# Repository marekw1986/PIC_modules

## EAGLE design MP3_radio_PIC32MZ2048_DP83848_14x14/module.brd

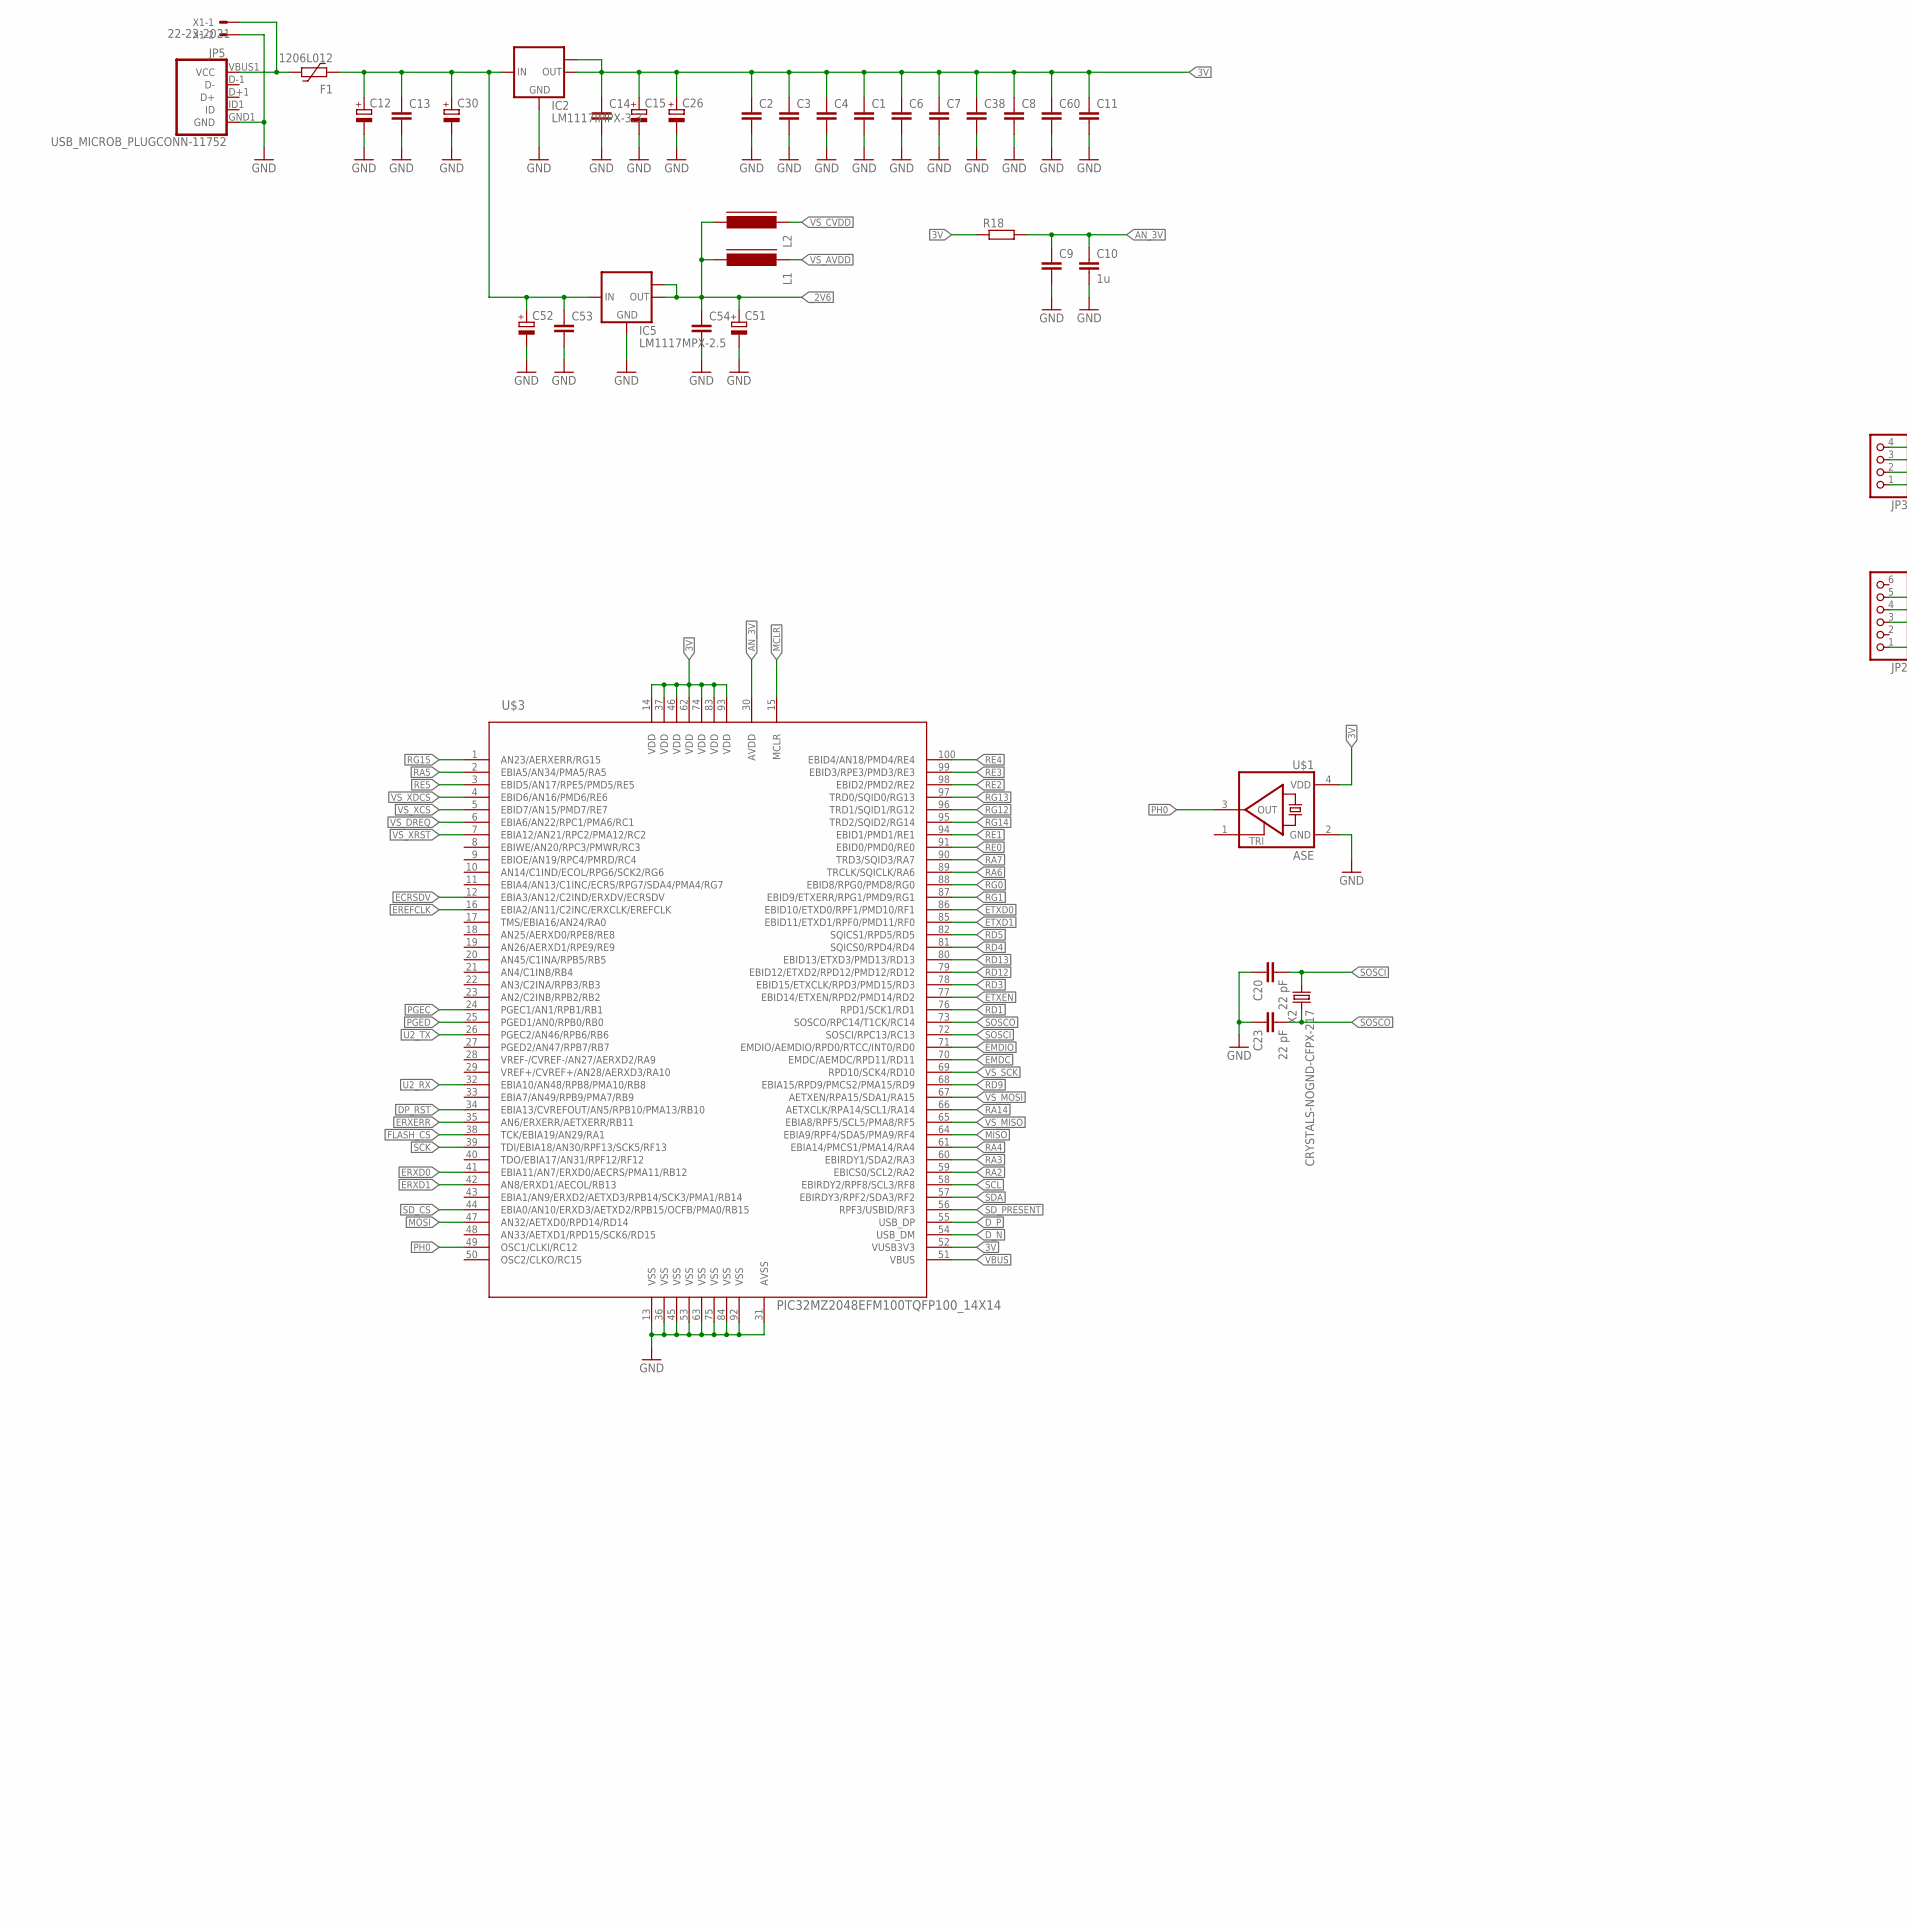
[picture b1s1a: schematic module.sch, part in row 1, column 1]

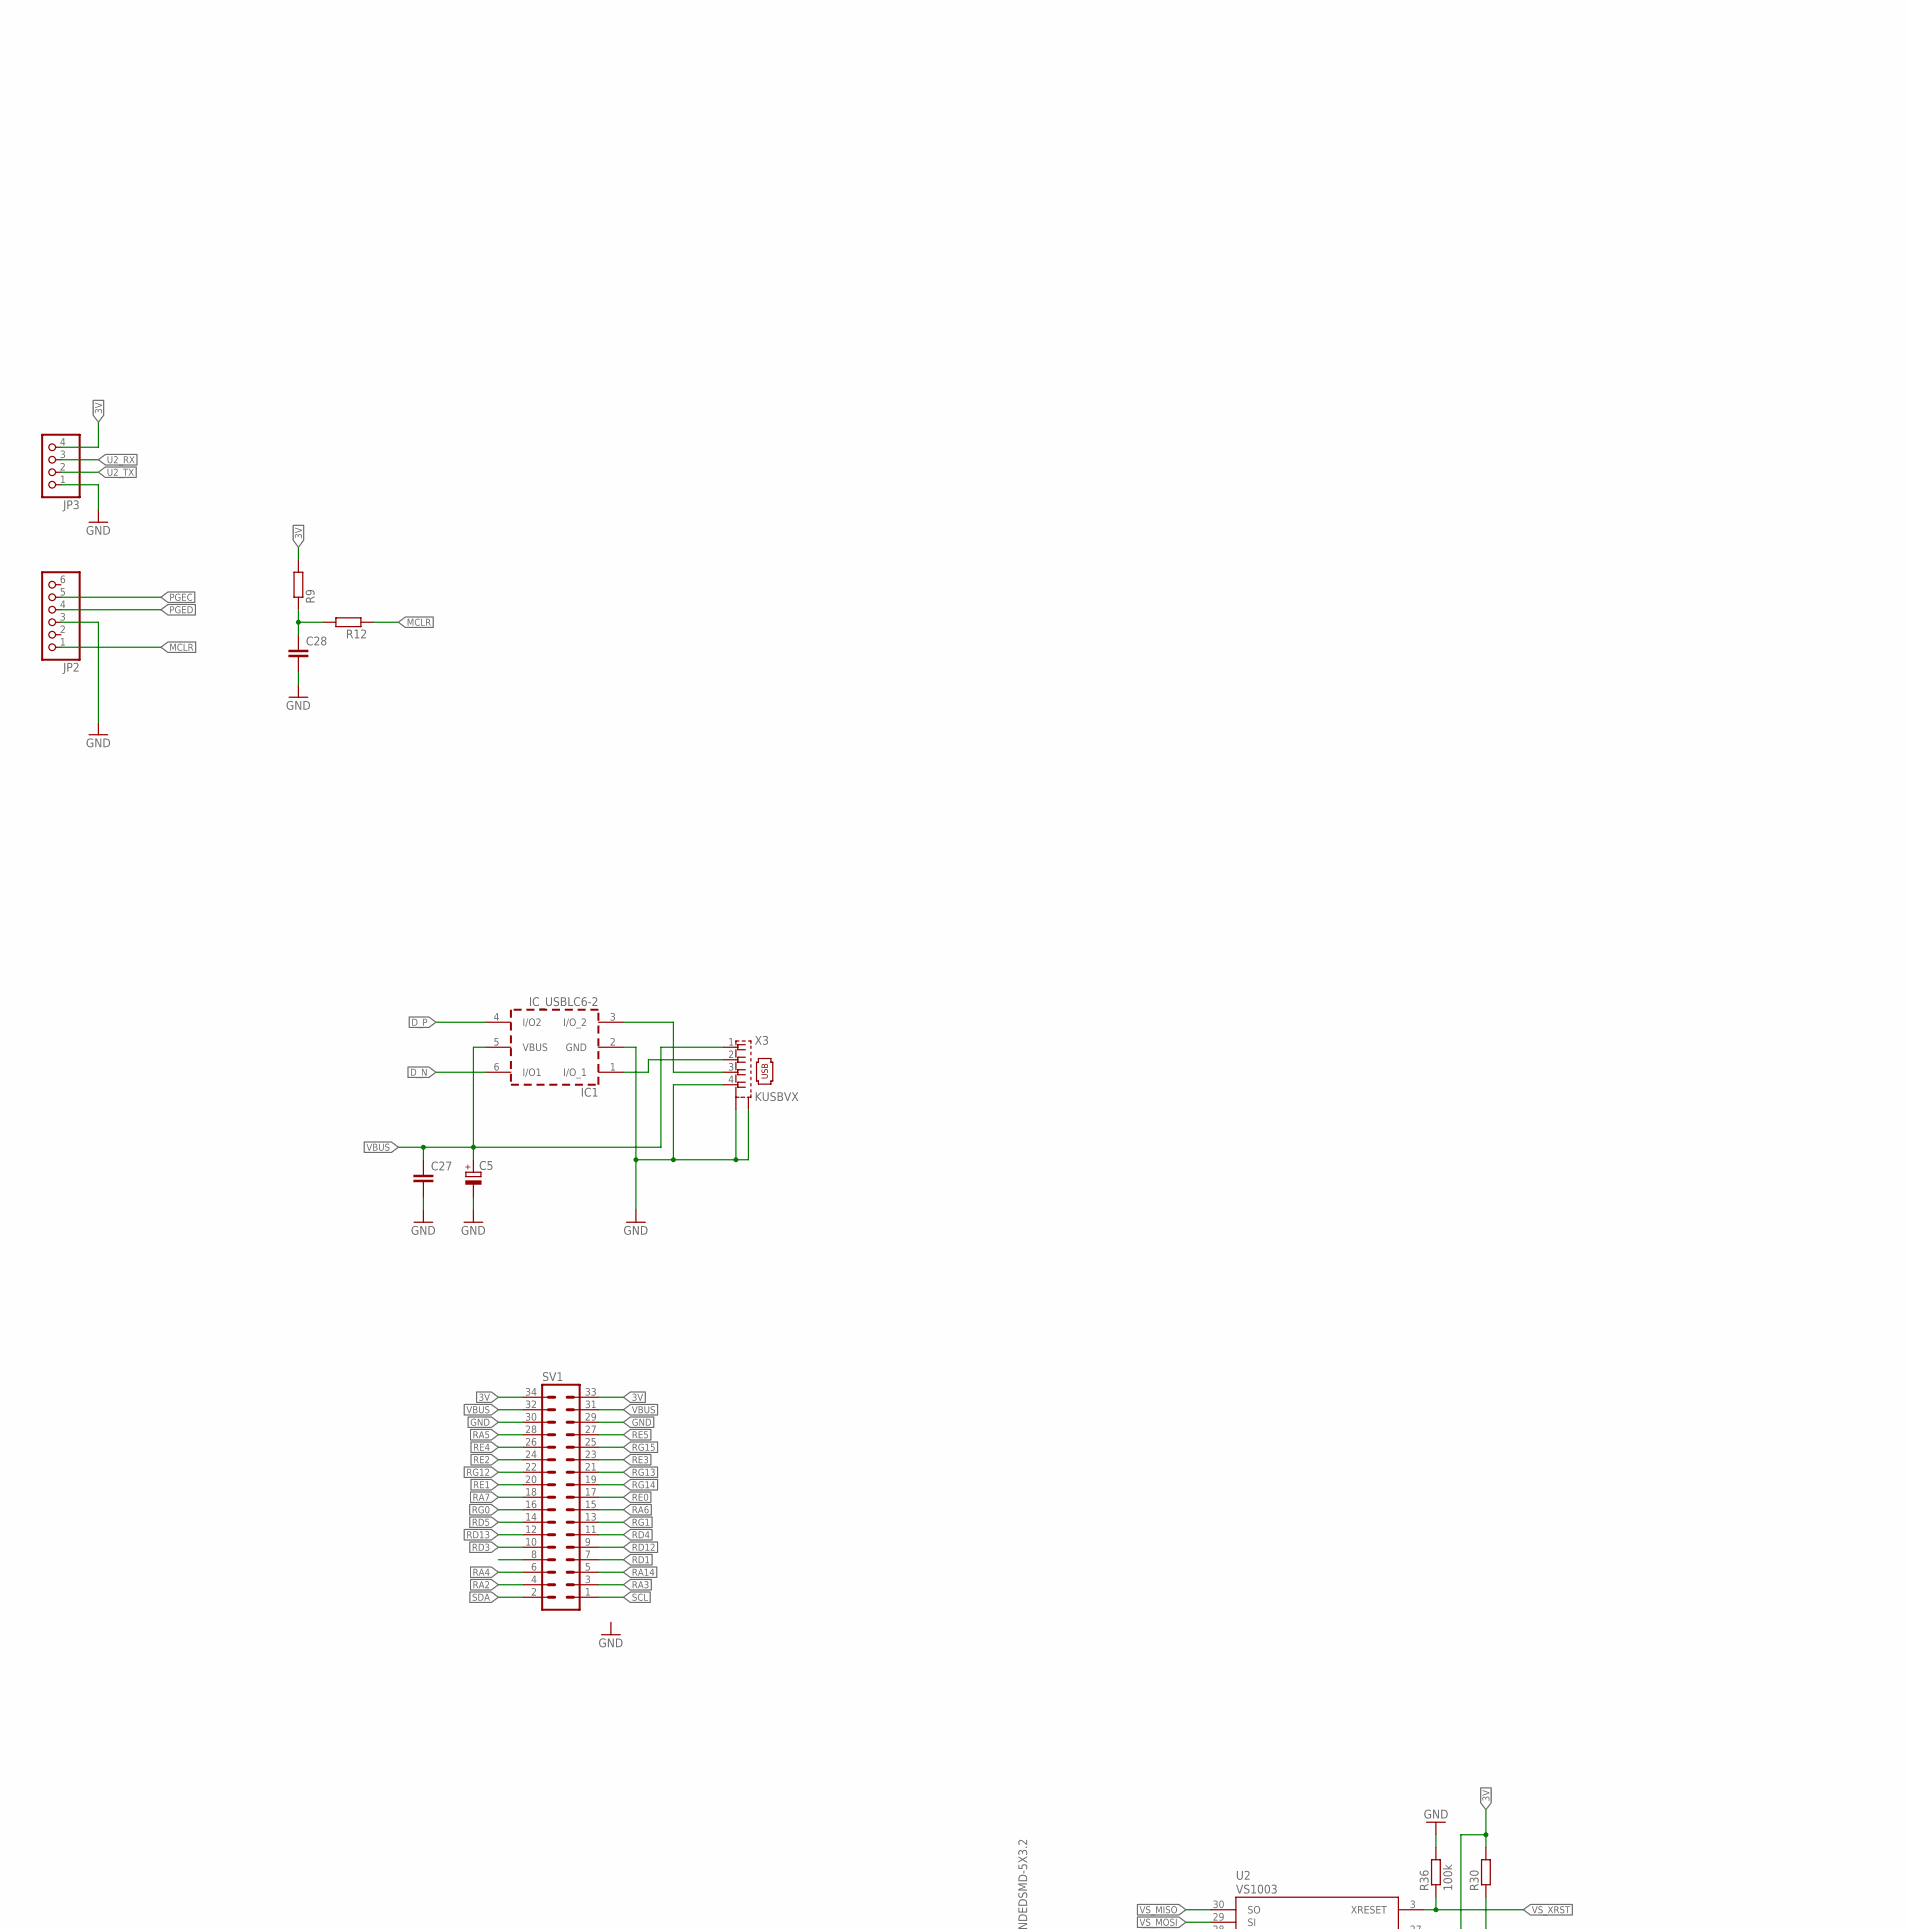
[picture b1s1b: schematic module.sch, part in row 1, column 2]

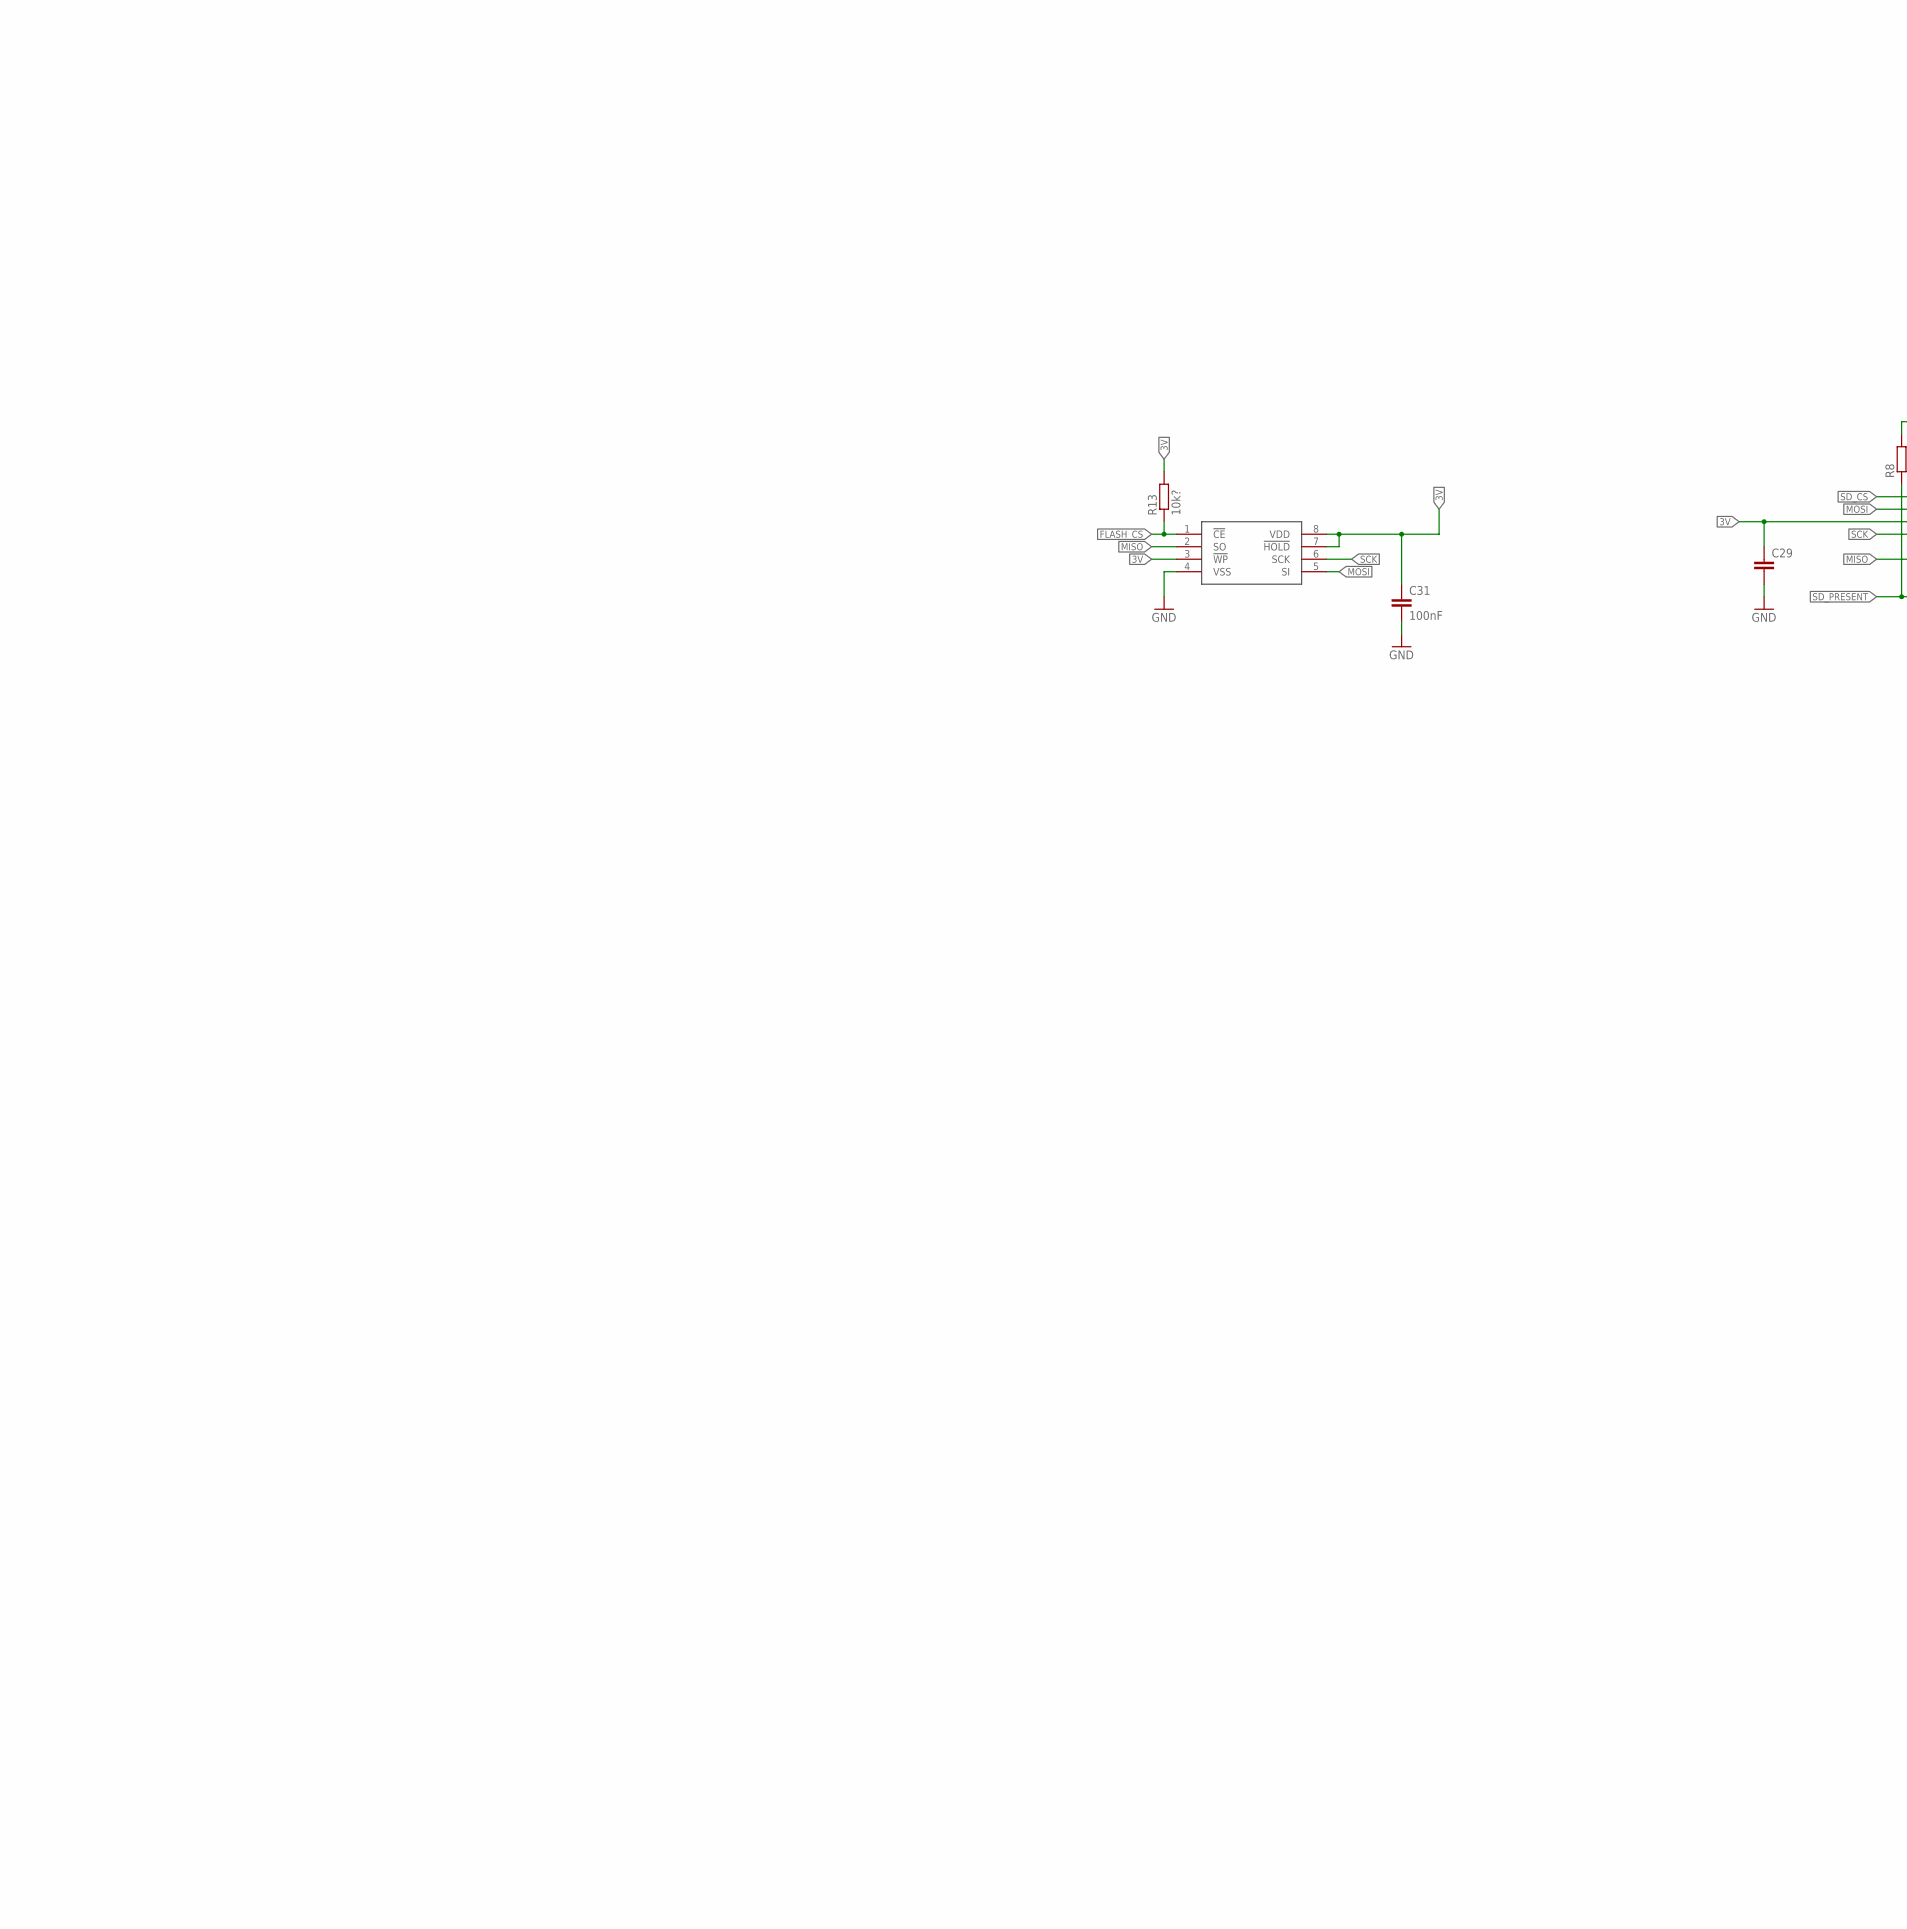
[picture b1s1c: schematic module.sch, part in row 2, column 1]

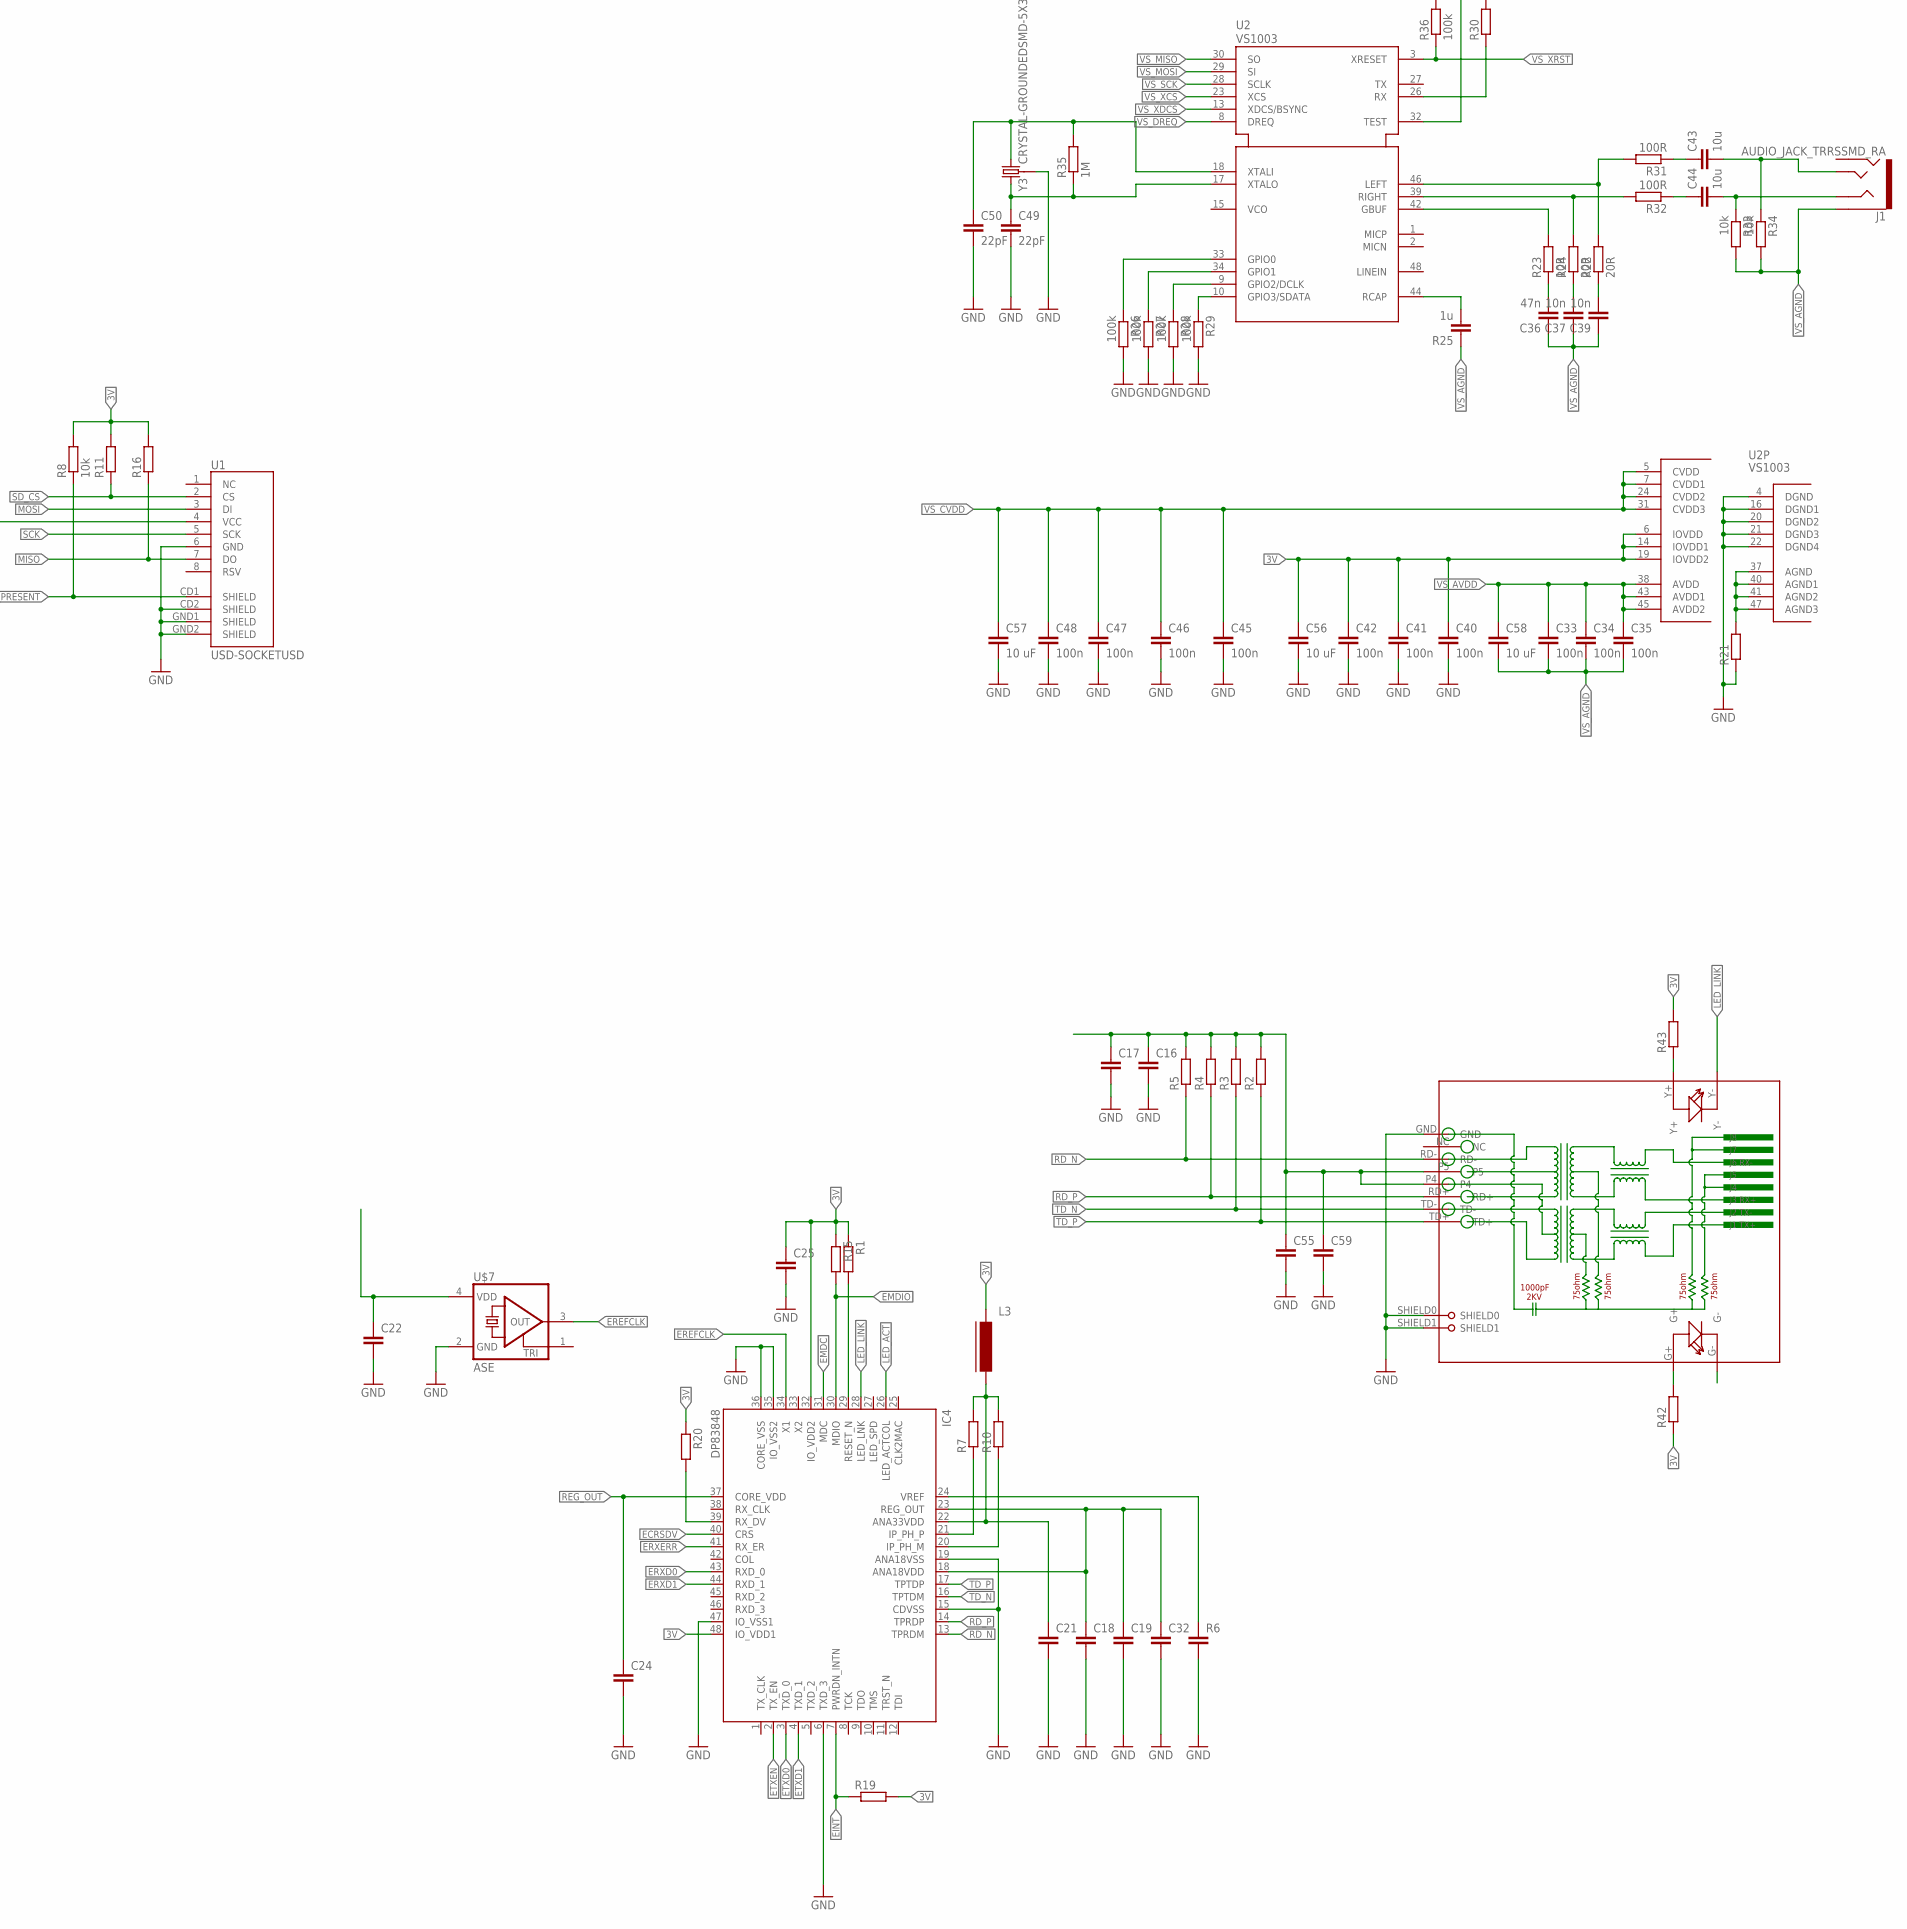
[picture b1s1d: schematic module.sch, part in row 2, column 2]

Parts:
C1, C2, C3, C4, C6, C7, C8, C9, C11, C18, C19, C21, C22, C38, C60: C-EUC0402; C0402
C5, C26, C30: CPOL-EUSMCA; SMC_A
C10: 1u; C0603
C12, C15, C51, C52: CPOL-EUSMCB; SMC_B
C13, C14, C16, C17, C24, C25, C27, C28, C29, C32, C55, C59: C-EUC0603; C0603
C20, C23: 22 pF; C0603
C31: 100nF; C0603
C33, C34, C35, C46, C47, C48: 100n; C0603
C36: 47n; C0603
C37, C39: 10n; C0603
C40, C41, C42, C45: 100n; C0402
C43, C44: 10u; C0603
C49, C50: 22pF; C0603
C53, C54: C-EUC1206; C1206
C56, C57, C58: 10 uF; C0603
F1: 1206L012; 1206L
IC1: IC_USBLC6-2; SOT-23-6L
IC2: LM1117IMPX-3.3; SOT223
IC4: DP83848; LQFP48
IC5: LM1117MPX-2.5; SOT223
J1: AUDIO_JACK_TRRSSMD_RA; AUDIO_JACK_3.5MM_TRRS_SMD_RA
JP2: PINHD-1X6; 1X06
JP3: PINHD-1X4; 1X04
JP5: USB_MICROB_PLUGCONN-11752; USB-B-MICRO-SMD_V03
L1, L2, L3: FERRITE-0805; FB805
R1, R7, R10, R12, R19: R-EU_R0402; R0402
R2, R3, R4, R5, R9, R11, R15, R16, R20, R21, R42, R43: R-EU_R0603; R0603
R6: C-EUC0603; C0603
R8, R33, R34: 10k; R0603
R13: 10k?; R0603
R18: R-EU_R0805; R0805
R22, R24: 20R; R0603
R23: 10R; R0603
R25: 1u; C0603
R26, R27, R28, R29: 100k; R0402
R30: R-EU_0204/7; 0204/7
R31, R32: 100R; R0603
R35: 1M; R0603
R36: 100k; R0603
RJ1: HR911105A
SV1: ML34L
U1: USD-SOCKETUSD; USD-SOCKET-PP
U2: VS1003; LQFP48
U$1, U$7: ASE
U$2: SST25VF016BSO8M; SO-08M
U$3: PIC32MZ2048EFM100TQFP100_14X14; TQFP100_14X14
X1: 22-23-2021
X2: CRYSTALS-NOGND-CFPX-217; 3.2X1.5-2-PAD
X3: KUSBVX
Y3: CRYSTAL-GROUNDEDSMD-5X3.2; CRYSTAL-SMD-5X3.2-4PAD

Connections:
3V: C1.1, C2.1, C3.1, C4.1, C6.1, C7.1, C8.1, C11.1, C14.1, C15.+, C22.1, C25.1, C26.+, C29.1, C31.1, C38.1, C40.1, C41.1, C42.1, C56.1, C60.1, IC2.2 (OUT), IC2.TAB (OUT1), IC4.32 (IO_VDD2), IC4.48 (IO_VDD1), JP3.4, L3.1, R1.1, R8.2, R9.2, R11.2, R13.2, R15.1, R16.2, R18.1, R19.2, R20.1, R30.2, R42.1, R43.2, SV1.33, SV1.34, U1.4 (VCC), U2.6 (IOVDD), U2.14 (IOVDD1), U2.19 (IOVDD2), U2.32 (TEST), U$1.4 (VDD), U$2.3 (!WP), U$2.7 (!HOLD), U$2.8 (VDD), U$3.14 (VDD), U$3.37 (VDD), U$3.46 (VDD), U$3.52 (VUSB3V3), U$3.62 (VDD), U$3.74 (VDD), U$3.83 (VDD), U$3.93 (VDD), U$7.4 (VDD)
A3V: C16.1, C17.1, C21.1, C55.1, C59.1, IC4.22 (ANA33VDD), L3.2, R2.2, R3.2, R4.2, R5.2, R7.2, R10.2, RJ1.P4, RJ1.P5
AN_3V: C9.1, C10.1, R18.2, U$3.30 (AVDD)
D2_N: IC1.1 (I/O_1), X3.2
D2_P: IC1.3 (I/O_2), X3.3
DP_RST: IC4.29 (RESET_N), R1.2, U$3.34 (EBIA13/CVREFOUT/AN5/RPB10/PMA13/RB10)
D_N: IC1.6 (I/O1), U$3.54 (USB_DM)
D_P: IC1.4 (I/O2), U$3.55 (USB_DP)
ECRSDV: IC4.40 (CRS), U$3.12 (EBIA3/AN12/C2IND/ERXDV/ECRSDV)
EINT: IC4.7 (PWRDN_INTN), R19.1
EMDC: IC4.31 (MDC), U$3.70 (EMDC/AEMDC/RPD11/RD11)
EMDIO: IC4.30 (MDIO), R15.2, U$3.71 (EMDIO/AEMDIO/RPD0/RTCC/INT0/RD0)
EREFCLK: IC4.34 (X1), U$3.16 (EBIA2/AN11/C2INC/ERXCLK/EREFCLK), U$7.3 (OUT)
ERXD0: IC4.43 (RXD_0), U$3.41 (EBIA11/AN7/ERXD0/AECRS/PMA11/RB12)
ERXD1: IC4.44 (RXD_1), U$3.42 (AN8/ERXD1/AECOL/RB13)
ERXERR: IC4.41 (RX_ER), U$3.35 (AN6/ERXERR/AETXERR/RB11)
ETXD0: IC4.3 (TXD_0), U$3.86 (EBID10/ETXD0/RPF1/PMD10/RF1)
ETXD1: IC4.4 (TXD_1), U$3.85 (EBID11/ETXD1/RPF0/PMD11/RF0)
ETXEN: IC4.2 (TX_EN), U$3.77 (EBID14/ETXEN/RPD2/PMD14/RD2)
FLASH_CS: R13.1, U$2.1 (!CE), U$3.38 (TCK/EBIA19/AN29/RA1)
GND: C1.2, C2.2, C3.2, C4.2, C5.-, C6.2, C7.2, C8.2, C9.2, C10.2, C11.2, C12.-, C13.2, C14.2, C15.-, C16.2, C17.2, C18.2, C19.2, C20.1, C21.2, C22.2, C23.1, C24.2, C25.2, C26.-, C27.2, C28.2, C29.2, C30.-, C31.2, C32.2, C38.2, C40.2, C41.2, C42.2, C45.2, C46.2, C47.2, C48.2, C49.2, C50.2, C51.-, C52.-, C53.2, C54.2, C55.2, C56.2, C57.2, C59.2, C60.2, IC1.2 (GND), IC2.1 (GND), IC4.6 (TXD_3), IC4.15 (CDVSS), IC4.19 (ANA18VSS), IC4.35 (IO_VSS2), IC4.36 (CORE_VSS), IC4.47 (IO_VSS1), IC5.1 (GND), JP2.3, JP3.1, JP5.GND1 (GND), R6.2, R21.1, R26.2, R27.2, R28.2, R29.2, R36.2, RJ1.GND, RJ1.SHIELD0, RJ1.SHIELD1, SV1.29, SV1.30, U1.6 (GND), U1.CD2 (SHIELD), U1.GND1 (SHIELD), U1.GND2 (SHIELD), U2.4 (DGND), U2.16 (DGND1), U2.20 (DGND2), U2.21 (DGND3), U2.22 (DGND4), U$1.2 (GND), U$2.4 (VSS), U$3.13 (VSS), U$3.31 (AVSS), U$3.36 (VSS), U$3.45 (VSS), U$3.53 (VSS), U$3.63 (VSS), U$3.75 (VSS), U$3.84 (VSS), U$3.92 (VSS), U$7.2 (GND), X1.2, X3.4, X3.M1 (S1), X3.M2 (S2), Y3.2 (3), Y3.4 (3)
LED_ACT: IC4.26 (LED_ACTCOL), RJ1.G-
LED_LINK: IC4.28 (LED_LNK), RJ1.Y-
MCLR: JP2.1, R12.1, U$3.15 (MCLR)
MISO: R16.1, U1.7 (DO), U$2.2 (SO), U$3.64 (EBIA9/RPF4/SDA5/PMA9/RF4)
MOSI: U1.3 (DI), U$2.5 (SI), U$3.47 (AN32/AETXD0/RPD14/RD14)
unnamed: IC4.21 (IP_PH_P), R7.1
unnamed: C28.1, R9.1, R12.2
unnamed: IC4.24 (VREF), R6.1
unnamed: IC4.20 (IP_PH_M), R10.1
unnamed: R42.2, RJ1.G+
unnamed: F1.1, JP5.VBUS1 (VCC), X1.1
unnamed: C36.2, R23.1
unnamed: R43.1, RJ1.Y+
PGEC: JP2.5, U$3.24 (PGEC1/AN1/RPB1/RB1)
PGED: JP2.4, U$3.25 (PGED1/AN0/RPB0/RB0)
PH0: U$1.3 (OUT), U$3.49 (OSC1/CLKI/RC12)
RA2: SV1.4, U$3.59 (EBICS0/SCL2/RA2)
RA3: SV1.3, U$3.60 (EBIRDY1/SDA2/RA3)
RA4: SV1.6, U$3.61 (EBIA14/PMCS1/PMA14/RA4)
RA5: SV1.28, U$3.2 (EBIA5/AN34/PMA5/RA5)
RA6: SV1.15, U$3.89 (TRCLK/SQICLK/RA6)
RA7: SV1.18, U$3.90 (TRD3/SQID3/RA7)
RA14: SV1.5, U$3.66 (AETXCLK/RPA14/SCL1/RA14)
RD1: SV1.7, U$3.76 (RPD1/SCK1/RD1)
RD3: SV1.10, U$3.78 (EBID15/ETXCLK/RPD3/PMD15/RD3)
RD4: SV1.11, U$3.81 (SQICS0/RPD4/RD4)
RD5: SV1.14, U$3.82 (SQICS1/RPD5/RD5)
RD9: SV1.8, U$3.68 (EBIA15/RPD9/PMCS2/PMA15/RD9)
RD12: SV1.9, U$3.79 (EBID12/ETXD2/RPD12/PMD12/RD12)
RD13: SV1.12, U$3.80 (EBID13/ETXD3/PMD13/RD13)
RD_N: IC4.13 (TPRDM), R5.1, RJ1.RD-
RD_P: IC4.14 (TPRDP), R4.1, RJ1.RD+
RE0: SV1.17, U$3.91 (EBID0/PMD0/RE0)
RE1: SV1.20, U$3.94 (EBID1/PMD1/RE1)
RE2: SV1.24, U$3.98 (EBID2/PMD2/RE2)
RE3: SV1.23, U$3.99 (EBID3/RPE3/PMD3/RE3)
RE4: SV1.26, U$3.100 (EBID4/AN18/PMD4/RE4)
RE5: SV1.27, U$3.3 (EBID5/AN17/RPE5/PMD5/RE5)
REG_OUT: C18.1, C19.1, C24.1, C32.1, IC4.18 (ANA18VDD), IC4.23 (REG_OUT), IC4.37 (CORE_VDD)
RG0: SV1.16, U$3.88 (EBID8/RPG0/PMD8/RG0)
RG1: SV1.13, U$3.87 (EBID9/ETXERR/RPG1/PMD9/RG1)
RG12: SV1.22, U$3.96 (TRD1/SQID1/RG12)
RG13: SV1.21, U$3.97 (TRD0/SQID0/RG13)
RG14: SV1.19, U$3.95 (TRD2/SQID2/RG14)
RG15: SV1.25, U$3.1 (AN23/AERXERR/RG15)
RX_DV: IC4.39 (RX_DV), R20.2
SCK: U1.5 (SCK), U$2.6 (SCK), U$3.39 (TDI/EBIA18/AN30/RPF13/SCK5/RF13)
SCL: SV1.1, U$3.58 (EBIRDY2/RPF8/SCL3/RF8)
SDA: SV1.2, U$3.57 (EBIRDY3/RPF2/SDA3/RF2)
SD_CS: R11.1, U1.2 (CS), U$3.44 (EBIA0/AN10/ERXD3/AETXD2/RPB15/OCFB/PMA0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)
SD_PRESENT: R8.1, U1.CD1 (SHIELD), U$3.56 (RPF3/USBID/RF3)
SOSCI: C20.2, U$3.72 (SOSCI/RPC13/RC13), X2.1
SOSCO: C23.2, U$3.73 (SOSCO/RPC14/T1CK/RC14), X2.2
TD_N: IC4.16 (TPTDM), R3.1, RJ1.TD-
TD_P: IC4.17 (TPTDP), R2.1, RJ1.TD+
U2_RX: JP3.3, U$3.32 (EBIA10/AN48/RPB8/PMA10/RB8)
U2_TX: JP3.2, U$3.26 (PGEC2/AN46/RPB6/RB6)
VBUS: C5.+, C12.+, C13.1, C27.1, C30.+, C52.+, C53.1, F1.2, IC1.5 (VBUS), IC2.3 (IN), IC5.3 (IN), SV1.31, SV1.32, U$3.51 (VBUS), X3.1
VS_AGND: C33.2, C34.2, C35.2, C36.1, C37.1, C39.1, C58.2, J1.EARTH, R21.2, R25.1, R33.2, R34.2, U2.37 (AGND), U2.40 (AGND1), U2.41 (AGND2), U2.47 (AGND3)
VS_AVDD: C33.1, C34.1, C35.1, C58.1, L1.1, U2.38 (AVDD), U2.43 (AVDD1), U2.45 (AVDD2)
VS_CVDD: C45.1, C46.1, C47.1, C48.1, C57.1, L2.1, U2.5 (CVDD), U2.7 (CVDD1), U2.24 (CVDD2), U2.31 (CVDD3)
VS_DREQ: U2.8 (DREQ), U$3.6 (EBIA6/AN22/RPC1/PMA6/RC1)
VS_MISO: U2.30 (SO), U$3.65 (EBIA8/RPF5/SCL5/PMA8/RF5)
VS_MOSI: U2.29 (SI), U$3.67 (AETXEN/RPA15/SDA1/RA15)
VS_N$9: C50.1, R35.2, U2.18 (XTALI), Y3.1 (2)
VS_N$13: C49.1, R35.1, U2.17 (XTALO), Y3.3 (1)
VS_N$14: R22.2, R31.2, U2.46 (LEFT)
VS_N$15: R23.2, U2.42 (GBUF)
VS_N$16: R24.2, R32.2, U2.39 (RIGHT)
VS_N$17: R25.2, U2.44 (RCAP)
VS_N$24: C37.2, R24.1
VS_N$25: C39.2, R22.1
VS_N$26: R29.1, U2.10 (GPIO3/SDATA)
VS_N$27: R28.1, U2.9 (GPIO2/DCLK)
VS_N$28: R27.1, U2.34 (GPIO1)
VS_N$30: R26.1, U2.33 (GPIO0)
VS_N$34: R30.1, U2.26 (RX)
VS_N$35: C43.1, R31.1
VS_N$36: C44.1, R32.1
VS_N$37: C44.2, J1.RING1, R33.1
VS_N$38: C43.2, J1.TIP, R34.1
VS_SCK: U2.28 (SCLK), U$3.69 (RPD10/SCK4/RD10)
VS_XCS: U2.23 (XCS), U$3.5 (EBID7/AN15/PMD7/RE7)
VS_XDCS: U2.13 (XDCS/BSYNC), U$3.4 (EBID6/AN16/PMD6/RE6)
VS_XRST: R36.1, U2.3 (XRESET), U$3.7 (EBIA12/AN21/RPC2/PMA12/RC2)
_2V6: C51.+, C54.1, IC5.2 (OUT), IC5.TAB (OUT1), L1.2, L2.2

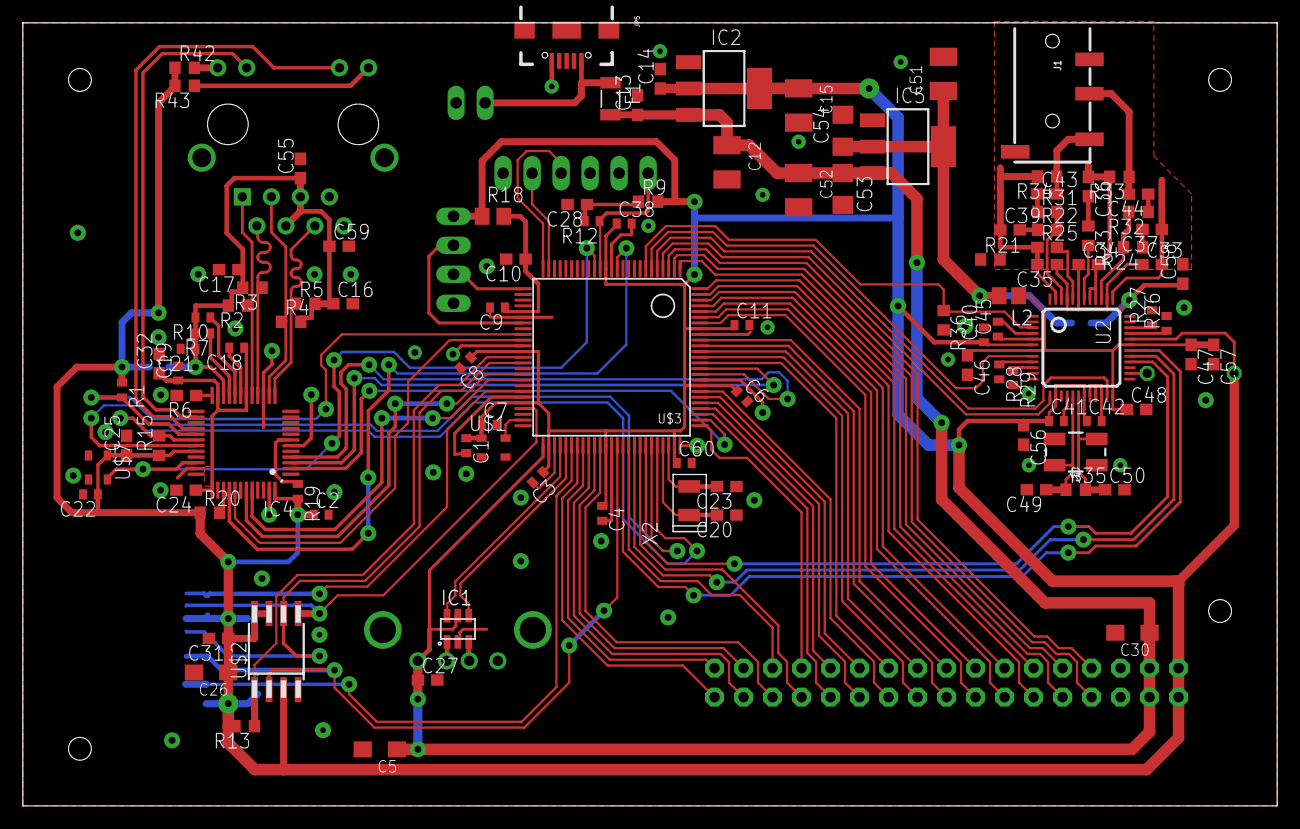
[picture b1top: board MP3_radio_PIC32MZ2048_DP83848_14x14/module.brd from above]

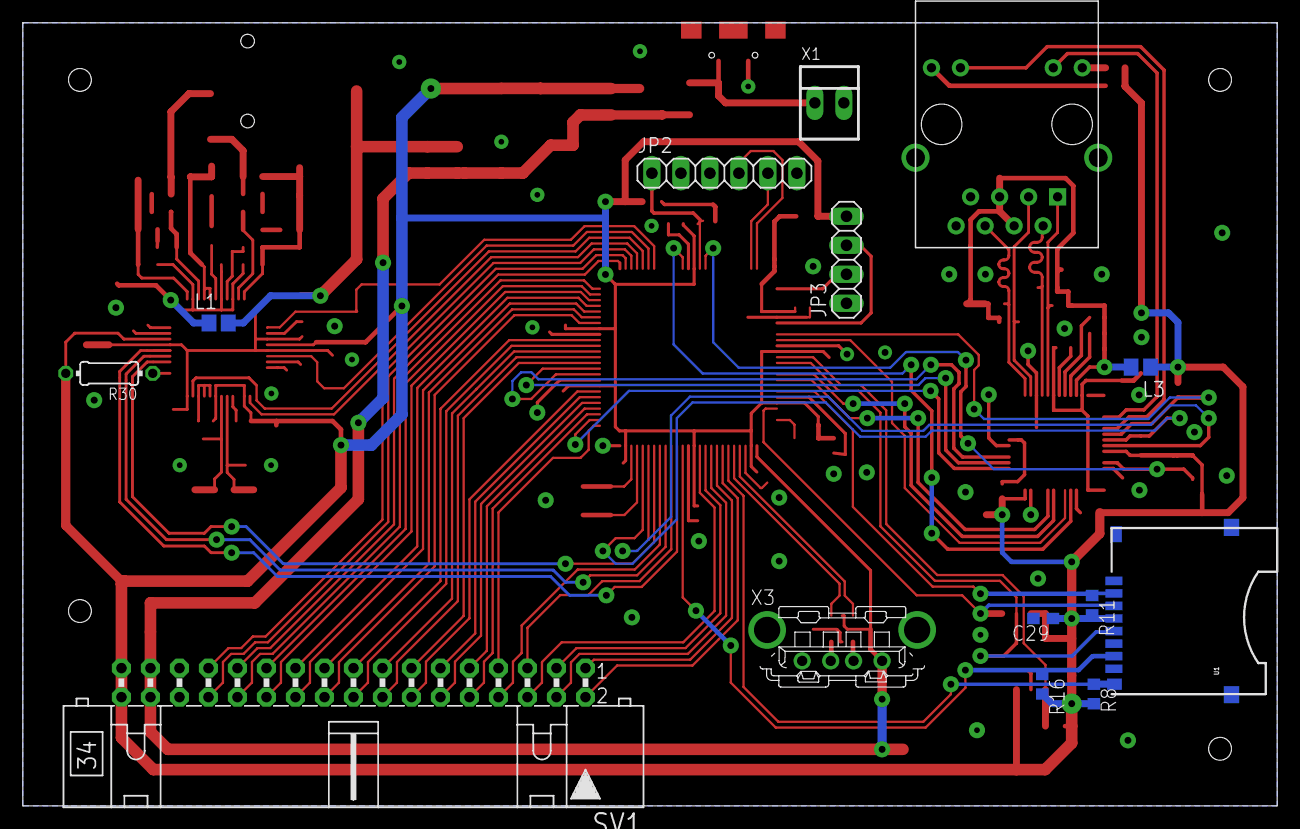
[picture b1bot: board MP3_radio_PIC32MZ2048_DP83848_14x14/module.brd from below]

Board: 2 copper layers, 109.9 x 68.6 mm, 120 parts (14 on the bottom side), 107 nets.

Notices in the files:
parts and their libraries:
SparkFun-Aesthetics: Licensing: Creative Commons ShareAlike 4.0 International - https://creativecommons.org/licenses/by-sa/4.0
